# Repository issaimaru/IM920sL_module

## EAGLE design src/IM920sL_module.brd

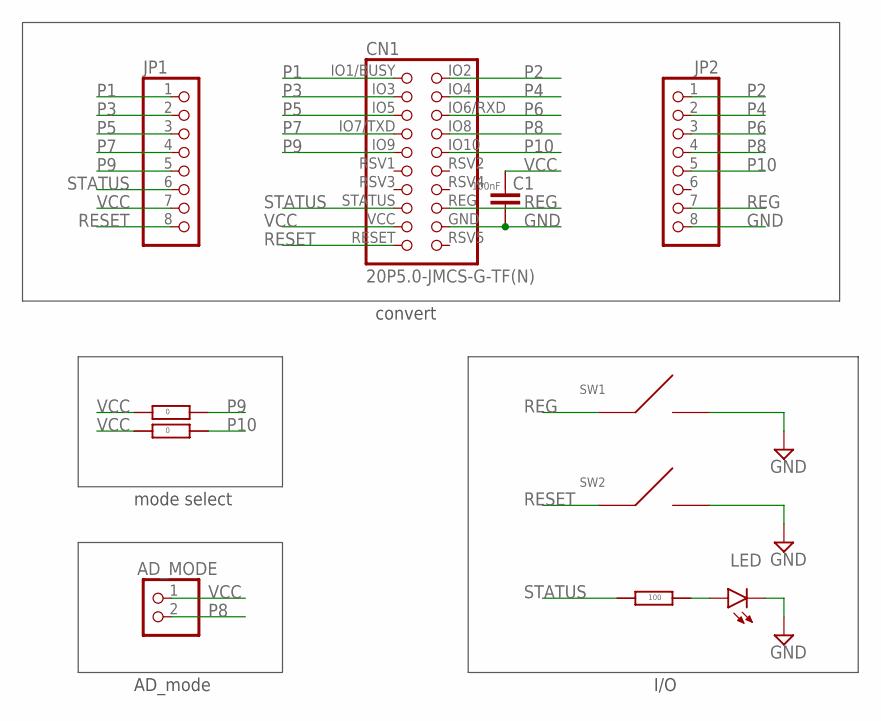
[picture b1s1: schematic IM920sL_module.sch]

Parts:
AD_MODE: PINHD-1X2; 1X02
C1: GCM188L81H104KA57
CN1: 20P5.0-JMCS-G-TF(N)
JP1, JP2: PINHD-1X8; 1X08
LED: SML-E12V8WT86
R1: RG2012N-101-B-T5; RG2012
R2, R3: RG2012-0Ω; RG2012
SW1, SW2: 一般的なタクトスイッチ

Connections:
GND: C1.P$2, CN1.GND, JP2.8, LED.K (C), SW1.T2, SW2.T2
unnamed: LED.A, R1.LEFT
P1: CN1.IO1/BUSY, JP1.1
P2: CN1.IO2, JP2.1
P3: CN1.IO3, JP1.2
P4: CN1.IO4, JP2.2
P5: CN1.IO5, JP1.3
P6: CN1.IO6/RXD, JP2.3
P7: CN1.IO7/TXD, JP1.4
P8: AD_MODE.2, CN1.IO8, JP2.4
P9: CN1.IO9, JP1.5, R2.LEFT
P10: CN1.IO10, JP2.5, R3.LEFT
REG: CN1.REG, JP2.7, SW1.T4
RESET: CN1.RESET, JP1.8, SW2.T4
STATUS: CN1.STATUS, JP1.6, R1.RIGHT
VCC: AD_MODE.1, C1.P$1, CN1.VCC, JP1.7, R2.RIGHT, R3.RIGHT

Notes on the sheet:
convert
mode select
AD_mode
I/O

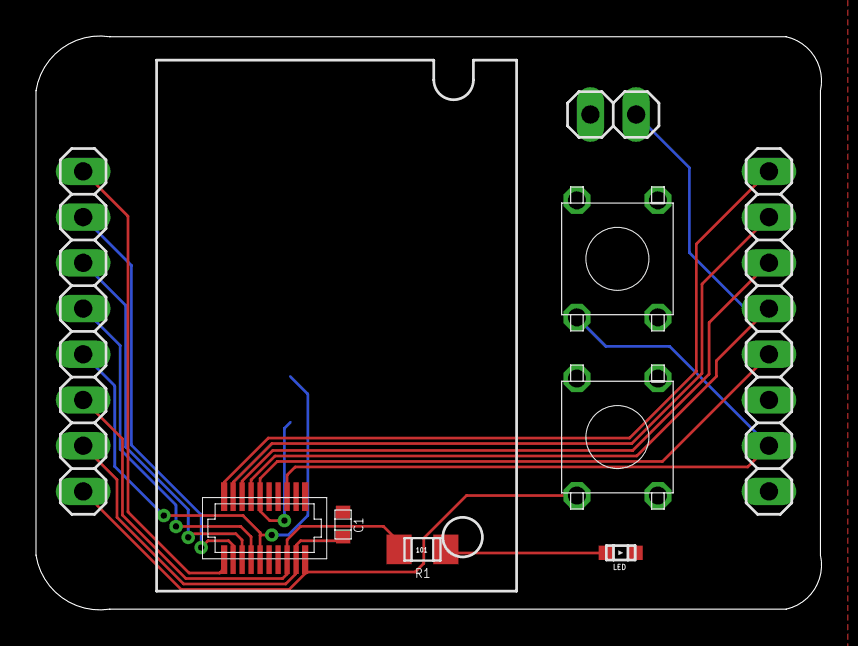
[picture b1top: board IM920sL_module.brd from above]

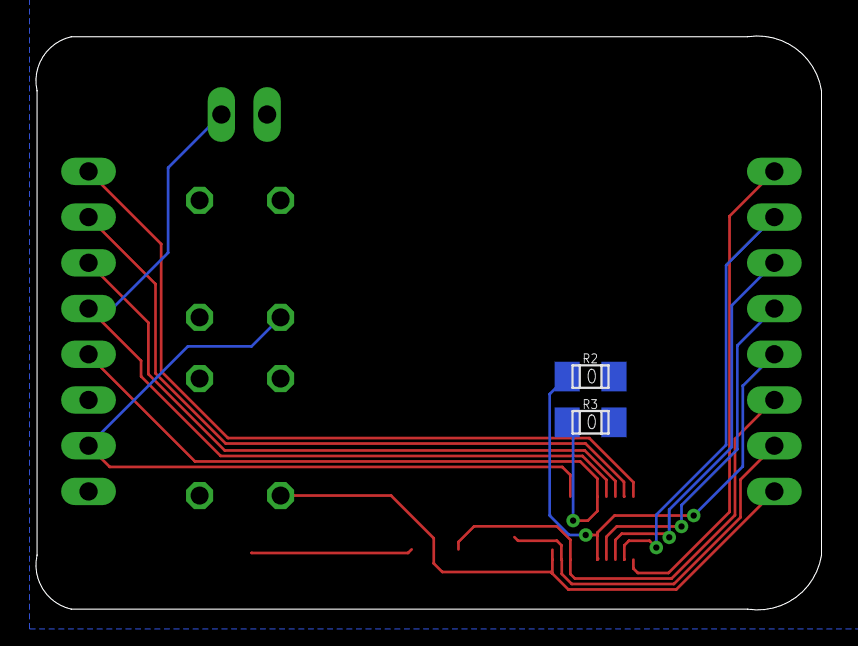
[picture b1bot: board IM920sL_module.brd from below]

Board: 2 copper layers, 43.6 x 31.9 mm, 11 parts (2 on the bottom side), 16 nets.

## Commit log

2022-10-30 回路図の完成
2022-10-30 Eagle移行前_配線図完成
2022-10-31 基板デザイン完成_gerber出力後
2022-10-31 基板デザインの改良
2022-10-31 基板デザインの改良2
